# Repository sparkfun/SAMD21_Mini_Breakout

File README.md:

SparkFun SAMD21 Mini Breakout
========================================

[*SparkFun SAMD21 Mini Breakout (DEV-13664)*](https://www.sparkfun.com/products/13664)

The SAMD21 Mini Breakout is a [Pro Mini](https://www.sparkfun.com/products/11114)-sized breakout for the Atmel [ATSAMD21G18](http://www.atmel.com/devices/ATSAMD21G18.aspx), a 32-bit ARM Cortex-M0+ processor with 256KB flash, 32KB SRAM, and an operating speed of up to 48MHz. The SAMD21 is compatible with the Arduino IDE, and libraries for the Arduino Zero.

Repository Contents
-------------------

* **/Documentation** - Data sheets, additional product information
* **/Firmware** - SAMD21 Arduino Bootloader
* **/Hardware** - Eagle design files (.brd, .sch)
* **/Production** - Production panel files (.brd)

Documentation
--------------
* **[Hookup Guide](https://learn.sparkfun.com/tutorials/samd21-minidev-breakout-hookup-guide/resources--going-further)** - Basic hookup guide for the SAMD21 Mini Breakout.

Product Versions
----------------
* [DEV-13664](https://www.sparkfun.com/products/13664) - Initial product release - v10.
* [DEV-13672](https://www.sparkfun.com/products/13672) - The SparkFun SAMD21 _Dev_ Breakout -- a similar, Arduino-shaped version of this board.

Version History
---------------
* [v1.0](https://github.com/sparkfun/SAMD21G_Mini_Breakout/tree/v10) - Initial release 

License Information
-------------------

This product is _**open source**_! 

Please review the LICENSE.md file for license information. 

If you have any questions or concerns on licensing, please contact techsupport@sparkfun.com.

Distributed as-is; no warranty is given.

- Your friends at SparkFun.

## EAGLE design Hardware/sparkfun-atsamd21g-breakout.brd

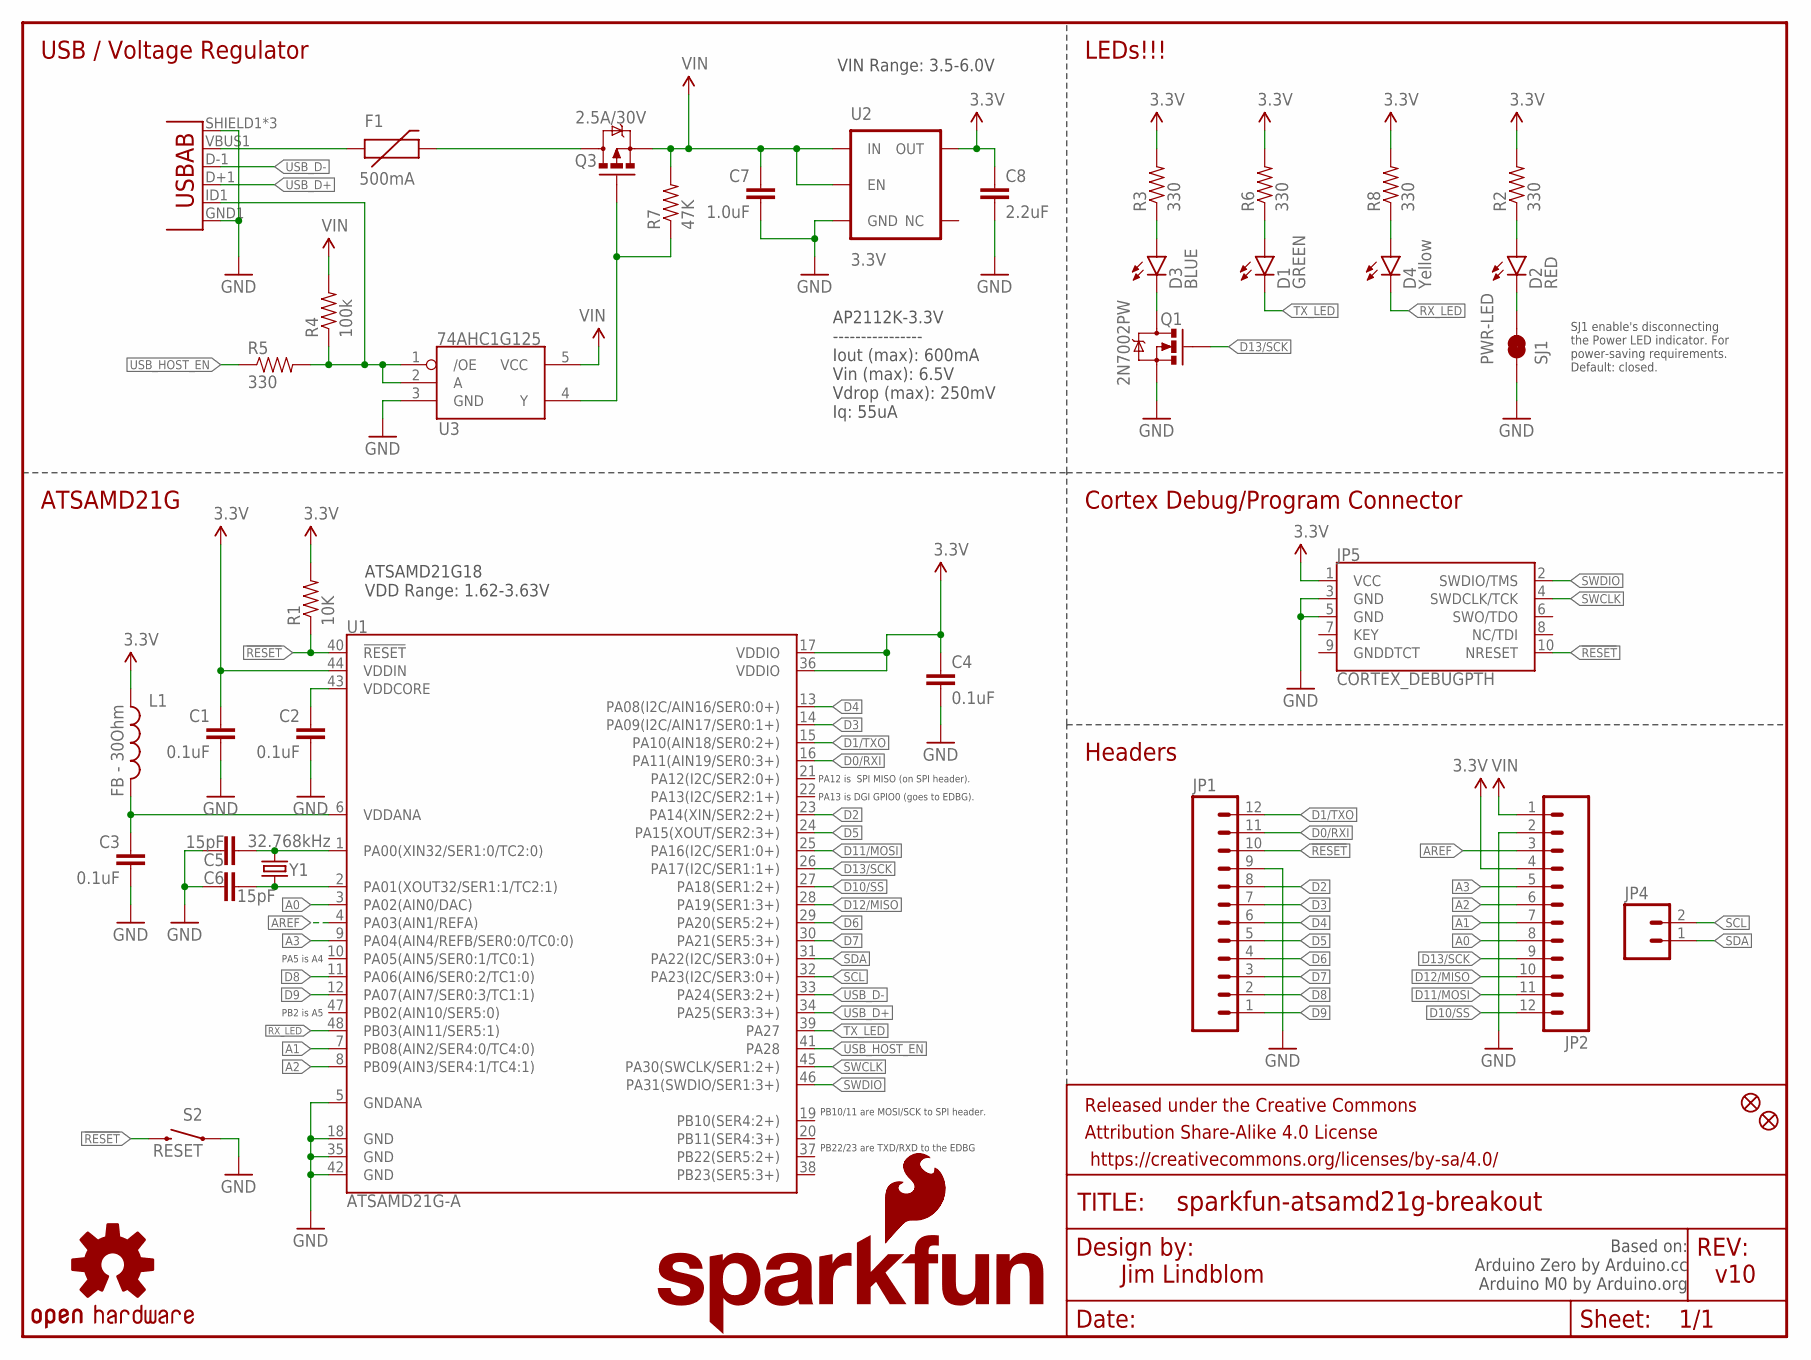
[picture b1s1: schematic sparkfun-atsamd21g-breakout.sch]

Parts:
C1, C2, C3, C4: 0.1uF; 0402-CAP
C5, C6: 15pF; 0402-CAP
C7: 1.0uF; 0805-CAP
C8: 2.2uF; 0603-CAP
D1: GREEN; LED-0603
D2: RED; LED-0603
D3: BLUE; LED-0603
D4: Yellow; LED-0603
F1: 500mA; PTC-1206
FID1, FID2: FIDUCIAL1X2; FIDUCIAL-1X2
FRAME1: FRAME-LETTER; CREATIVE_COMMONS
JP1, JP2: M12NO_SILK; 1X12_NO_SILK
JP3: USB-ABCONN-11794; USB-AB-MICRO-SMD_V03
JP4: M021X02_NO_SILK; 1X02_NO_SILK
JP5: CORTEX_DEBUGPTH; 2X5-PTH-1.27MM
L1: FB - 30Ohm; 0603
LOGO1: SFE_LOGO_FLAME.1_INCH; SFE_LOGO_FLAME_.1
LOGO2: OSHW-LOGOS; OSHW-LOGO-S
LOGO3: SFE_LOGO_NAME_FLAME.1_INCH; SFE_LOGO_NAME_FLAME_.1
Q1: 2N7002PW; SOT323
Q3: 2.5A/30V; SOT23-3
R1: 10K; 0603-RES
R2, R3, R5, R6, R8: 330; 0603-RES
R4: 100k; 0603-RES
R7: 47K; 0603-RES
S2: RESET; TACTILE_SWITCH_SMD_4.6X2.8MM
SJ1: PWR-LED; PAD-JUMPER-2-NC_BY_TRACE_NO_SILK
U1: ATSAMD21G-A; TQFP-48
U2: 3.3V; SOT23-5
U3: 74AHC1G125; SOT23-5
Y1: 32.768kHz; CRYSTAL-SMD-3.2X1.5MM

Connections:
3.3V: C1.1, C4.1, C8.1, JP2.4, JP5.1 (VCC), L1.1, R1.2, R2.2, R3.2, R6.2, R8.2, U1.17 (VDDIO), U1.36 (VDDIO), U1.44 (VDDIN), U2.5 (OUT)
!RESET: JP1.10, JP5.10 (NRESET), R1.1, S2.3 (2), S2.4 (2), U1.40 (!RESET!)
A0: JP2.8, U1.3 (PA02(AIN0/DAC))
A1: JP2.7, U1.7 (PB08(AIN2/SER4:0/TC4:0))
A2: JP2.6, U1.8 (PB09(AIN3/SER4:1/TC4:1))
A3: JP2.5, U1.9 (PA04(AIN4/REFB/SER0:0/TC0:0))
AREF: JP2.3, U1.4 (PA03(AIN1/REFA))
D0/RXI: JP1.11, U1.16 (PA11(AIN19/SER0:3+))
D1/TXO: JP1.12, U1.15 (PA10(AIN18/SER0:2+))
D2: JP1.8, U1.23 (PA14(XIN/SER2:2+))
D3: JP1.7, U1.14 (PA09(I2C/AIN17/SER0:1+))
D4: JP1.6, U1.13 (PA08(I2C/AIN16/SER0:0+))
D5: JP1.5, U1.24 (PA15(XOUT/SER2:3+))
D6: JP1.4, U1.29 (PA20(SER5:2+))
D7: JP1.3, U1.30 (PA21(SER5:3+))
D8: JP1.2, U1.11 (PA06(AIN6/SER0:2/TC1:0))
D9: JP1.1, U1.12 (PA07(AIN7/SER0:3/TC1:1))
D10/SS: JP2.12, U1.27 (PA18(SER1:2+))
D11/MOSI: JP2.11, U1.25 (PA16(I2C/SER1:0+))
D12/MISO: JP2.10, U1.28 (PA19(SER1:3+))
D13/SCK: JP2.9, Q1.1 (G), U1.26 (PA17(I2C/SER1:1+))
GND: C1.2, C2.2, C3.2, C4.2, C5.1, C6.2, C7.2, C8.2, JP1.9, JP2.2, JP3.GND1 (GND), JP3.SHIELD1 (SHIELD), JP3.SHIELD2 (SHIELD), JP3.SHIELD3 (SHIELD), JP5.3 (GND), JP5.5 (GND), Q1.2 (S), S2.1, S2.2 (1), SJ1.1, U1.5 (GNDANA), U1.18 (GND), U1.35 (GND), U1.42 (GND), U2.2 (GND), U3.3 (GND)
unnamed: F1.1, JP3.VBUS1 (VBUS)
unnamed: C5.2, U1.1 (PA00(XIN32/SER1:0/TC2:0)), Y1.P$2 (2)
unnamed: D3.C, Q1.3 (D)
unnamed: C6.1, U1.2 (PA01(XOUT32/SER1:1/TC2:1)), Y1.P$1 (1)
unnamed: D2.A, R2.1
unnamed: D3.A, R3.1
unnamed: F1.2, Q3.3 (D)
unnamed: JP3.ID1 (USBID), R4.1, R5.2, U3.1 (/OE), U3.2 (A)
unnamed: Q3.1 (G), R7.1, U3.4 (Y)
unnamed: D1.A, R6.1
unnamed: D4.A, R8.1
unnamed: D2.C, SJ1.2
RX_LED: D4.C, U1.48 (PB03(AIN11/SER5:1))
SCL: JP4.2, U1.32 (PA23(I2C/SER3:0+))
SDA: JP4.1, U1.31 (PA22(I2C/SER3:0+))
SWCLK: JP5.4 (SWDCLK/TCK), U1.45 (PA30(SWCLK/SER1:2+))
SWDIO: JP5.2 (SWDIO/TMS), U1.46 (PA31(SWDIO/SER1:3+))
TX_LED: D1.C, U1.39 (PA27)
USB_D+: JP3.D+1 (D+), U1.34 (PA25(SER3:3+))
USB_D-: JP3.D-1 (D-), U1.33 (PA24(SER3:2+))
USB_HOST_EN: R5.1, U1.41 (PA28)
VDDANA: C3.1, L1.2, U1.6 (VDDANA)
VDDCORE: C2.1, U1.43 (VDDCORE)
VIN: C7.1, JP2.1, Q3.2 (S), R4.2, R7.2, U2.1 (IN), U2.3 (EN), U3.5 (VCC)

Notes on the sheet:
PB22/23 are TXD/RXD to the EDBG
PB10/11 are MOSI/SCK to SPI header.
PA12 is SPI MISO (on SPI header).
PA13 is DGI GPIO0 (goes to EDBG).
PA5 is A4
PB2 is A5
USB / Voltage Regulator
LEDs!!!
Cortex Debug/Program Connector
Headers
ATSAMD21G
Jim Lindblom
v10
ATSAMD21G18 VDD Range: 1.62-3.63V
SJ1 enable's disconnecting the Power LED indicator. For power-saving requirements. Default: closed.
VIN Range: 3.5-6.0V
Based on: Arduino Zero by Arduino.cc Arduino M0 by Arduino.org
AP2112K-3.3V ---------------- Iout (max): 600mA Vin (max): 6.5V Vdrop (max): 250mV Iq: 55uA

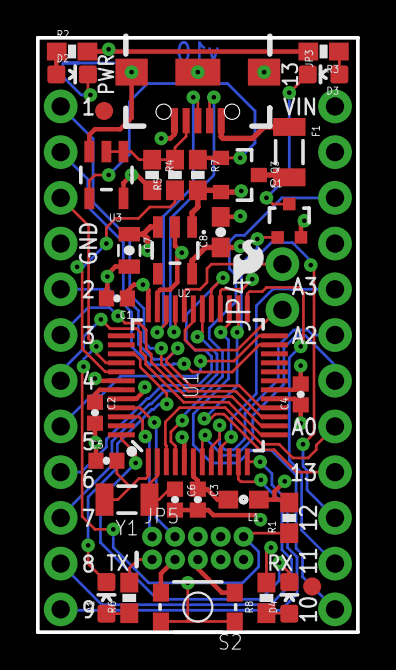
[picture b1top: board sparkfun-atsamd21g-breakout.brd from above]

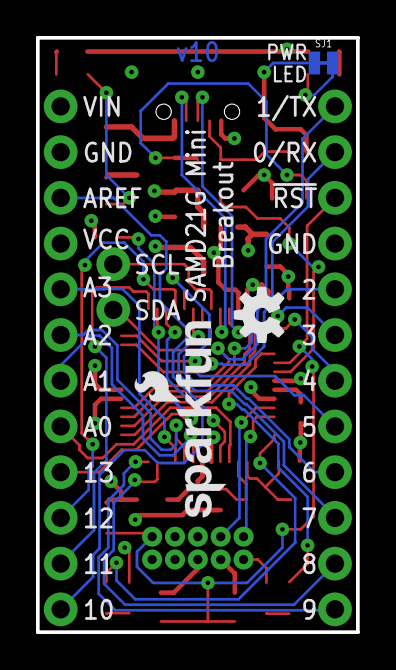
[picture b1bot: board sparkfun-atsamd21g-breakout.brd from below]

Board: 4 copper layers, 17.8 x 33.0 mm, 41 parts (3 on the bottom side), 46 nets.

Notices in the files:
parts and their libraries:
SparkFun-Connectors: Licensing: Creative Commons ShareAlike 4.0 International - https://creativecommons.org/licenses/by-sa/4.0
SparkFun-Aesthetics: Released under the Creative Commons Attribution Share-Alike 4.0 License
SparkFun-Aesthetics: https://creativecommons.org/licenses/by-sa/4.0
